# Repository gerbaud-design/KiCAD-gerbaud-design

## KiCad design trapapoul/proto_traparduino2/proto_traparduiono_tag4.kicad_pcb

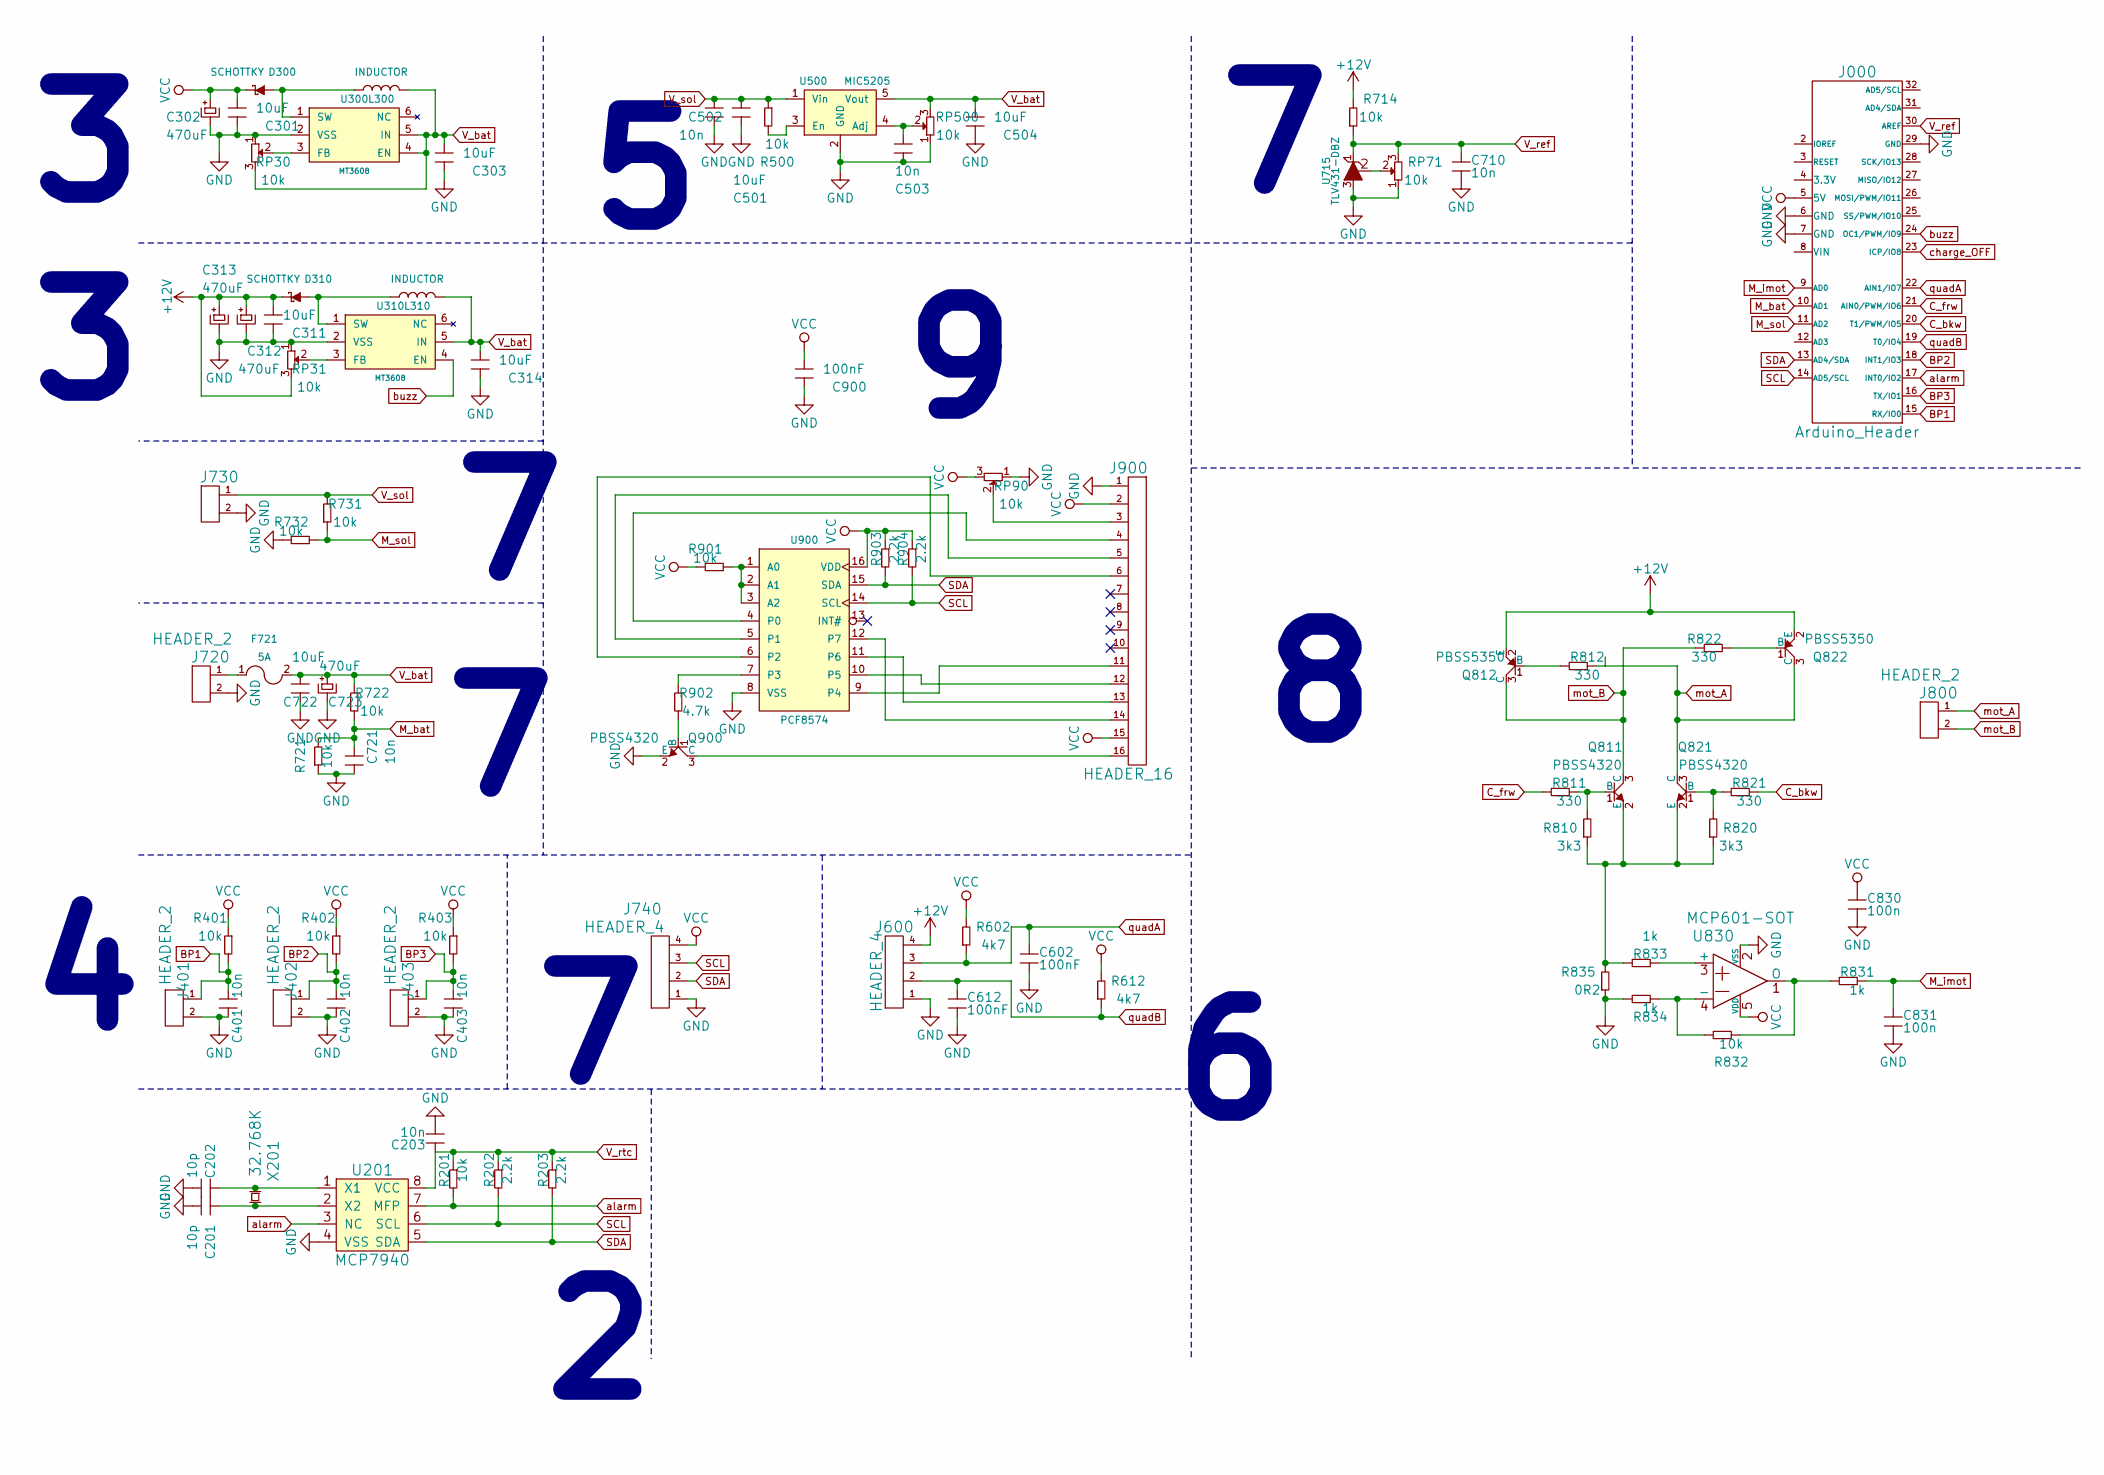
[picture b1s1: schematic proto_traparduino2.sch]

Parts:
C201, C202: 10p; C_1206_HandSoldering
C203, C401, C402, C403, C502, C503, C710, C721: 10n; C_1206_HandSoldering
C301, C303, C311, C314, C501, C504, C722: 10uF; C_1206_HandSoldering
C302, C312, C313, C723: 470uF; C_Radial_D8_L11.5_P3.5
C602, C612, C900: 100nF; C_1206_HandSoldering
C830, C831: 100n; C_1206_HandSoldering
D300, D310: SCHOTTKY; MiniMELF_Handsoldering
F721: 5A; Fuse_SMD1206_HandSoldering
J000: Arduino_Header; arduino_header
J401, J402, J403, J720, J730, J800: HEADER_2; Pin_Header_Straight_1x02
J600, J740: HEADER_4; Pin_Header_Straight_1x04
J900: HEADER_16; Pin_Header_Straight_1x16
L300, L310: INDUCTOR; R_1206_HandSoldering
Q811, Q821, Q900: PBSS4320; SOT-23_Handsoldering
Q812, Q822: PBSS5350; SOT-23_Handsoldering
R201, R401, R402, R403, R500, R714, R721, R722, R731, R732, R832, R901: 10k; R_1206_HandSoldering
R202, R203, R903, R904: 2.2k; R_1206_HandSoldering
R602, R612: 4k7; R_1206_HandSoldering
R810, R820: 3k3; R_1206_HandSoldering
R811, R812, R821, R822: 330; R_1206_HandSoldering
R831, R833, R834: 1k; R_1206_HandSoldering
R835: 0R2; R_1206_HandSoldering
R902: 4.7k; R_1206_HandSoldering
RP30, RP31, RP71, RP90, RP500: 10k; Potentiometer_Triwood_RM-065
U201: MCP7940; SOIC-8-N
U300, U310: MT3608; SOT-23-6_Handsoldering
U500: MIC5205; SOT-23-5_Handsoldering
U715: TLV431-DBZ; SOT-23_Handsoldering
U830: MCP601-SOT; SOT-23-5_Handsoldering
U900: PCF8574; SO-16-W
X201: 32.768K; Crystal_Round_Vertical_3mm_BigPad

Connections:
+12V: C311.1, C312.1, C313.1, D310.2 (K), J600.4, Q812.2 (E), Q822.2 (E), R714.2, RP31.3
BP1: C401.1, J000.15 (RX/IO0), J401.1, R401.2
BP2: C402.1, J000.18 (INT1/IO3), J402.1, R402.2
BP3: C403.1, J000.16 (TX/IO1), J403.1, R403.2
C_bkw: J000.20 (T1/PWM/IO5), R821.1
C_frw: J000.21 (AIN0/PWM/IO6), R811.2
GND: C201.2, C202.2, C203.2, C301.2, C302.2, C303.2, C311.2, C312.2, C313.2, C314.2, C401.2, C402.2, C403.2, C501.2, C502.2, C503.2, C504.2, C602.2, C612.2, C710.2, C721.2, C722.2, C723.2, C830.2, C831.2, C900.2, J000.6 (GND), J000.7 (GND), J000.29 (GND), J401.2, J402.2, J403.2, J600.1, J720.2, J730.2, J740.1, J900.1, Q900.2 (E), R721.1, R732.2, R834.2, R835.1, RP30.1, RP31.1, RP71.1, RP90.1, RP500.1, U201.4 (VSS), U300.2 (VSS), U310.2 (VSS), U500.2 (GND), U715.3 (A), U830.2 (VSS), U900.8 (VSS)
M_bat: C721.1, J000.10 (AD1), R721.2, R722.2
M_imot: C831.1, J000.9 (AD0), R831.1
M_sol: J000.11 (AD2), R731.1, R732.1
unnamed: C201.1, U201.2 (X2), X201.2
unnamed: C202.1, U201.1 (X1), X201.1
unnamed: C503.1, RP500.2, U500.4 (Adj)
unnamed: D300.1 (A), L300.1, U300.1 (SW)
unnamed: D310.1 (A), L310.1, U310.1 (SW)
unnamed: F721.1, J720.1
unnamed: J900.3, RP90.2
unnamed: J900.4, U900.4 (P0)
unnamed: J900.5, U900.5 (P1)
unnamed: J900.6, U900.6 (P2)
unnamed: J900.11, U900.9 (P4)
unnamed: J900.12, U900.10 (P5)
unnamed: J900.13, U900.11 (P6)
unnamed: J900.14, U900.12 (P7)
unnamed: J900.16, Q900.3 (C)
unnamed: Q811.1 (B), R810.2, R811.1
unnamed: Q811.2 (E), Q821.2 (E), R810.1, R820.1, R833.2, R835.2
unnamed: Q812.1 (B), R812.2
unnamed: Q821.1 (B), R820.2, R821.2
unnamed: Q822.1 (B), R822.2
unnamed: Q900.1 (B), R902.2
unnamed: R500.2, U500.3 (En)
unnamed: R831.2, R832.1, U830.1 (O)
unnamed: R832.2, R834.1, U830.4 (-)
unnamed: R833.1, U830.3 (+)
unnamed: R901.1, U900.1 (A0), U900.2 (A1), U900.3 (A2)
unnamed: R902.1, U900.7 (P3)
unnamed: RP30.2, U300.3 (FB)
unnamed: RP31.2, U310.3 (FB)
unnamed: RP71.2, U715.2 (Ref)
SCL: J000.14 (AD5/SCL), J740.3, R202.2, R904.2, U201.6 (SCL), U900.14 (SCL)
SDA: J000.13 (AD4/SDA), J740.2, R203.2, R903.2, U201.5 (SDA), U900.15 (SDA)
VCC: C301.1, C302.1, C830.1, C900.1, D300.2 (K), J000.5 (5V), J740.4, J900.2, J900.15, R401.1, R402.1, R403.1, R602.2, R612.2, R901.2, R903.1, R904.1, RP90.3, U830.5 (VDD), U900.16 (VDD)
V_bat: C303.1, C314.1, C504.1, C722.1, C723.1, F721.2, L300.2, L310.2, R722.1, RP30.3, RP500.3, U300.4 (EN), U300.5 (IN), U310.5 (IN), U500.5 (Vout)
V_ref: C710.1, J000.30 (AREF), R714.1, RP71.3, U715.1 (K)
V_rtc: C203.1, R201.1, R202.1, R203.1, U201.8 (VCC)
V_sol: C501.1, C502.1, J730.1, R500.1, R731.2, U500.1 (Vin)
alarm: J000.17 (INT0/IO2), R201.2, U201.3 (NC), U201.7 (MFP)
buzz: J000.24 (OC1/PWM/IO9), U310.4 (EN)
mot_A: J800.1, Q821.3 (C), Q822.3 (C), R812.1
mot_B: J800.2, Q811.3 (C), Q812.3 (C), R822.1
quadA: C602.1, J000.22 (AIN1/IO7), J600.3, R602.1
quadB: C612.1, J000.19 (T0/IO4), J600.2, R612.1

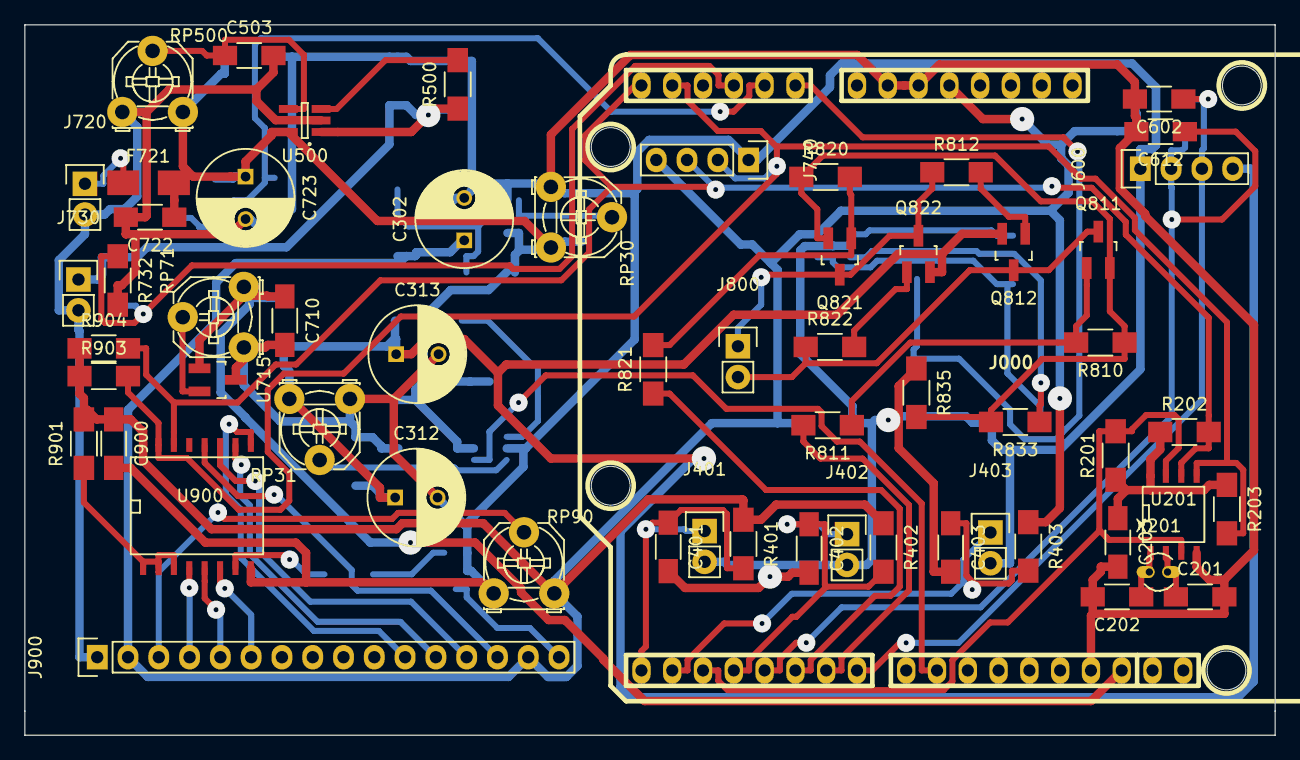
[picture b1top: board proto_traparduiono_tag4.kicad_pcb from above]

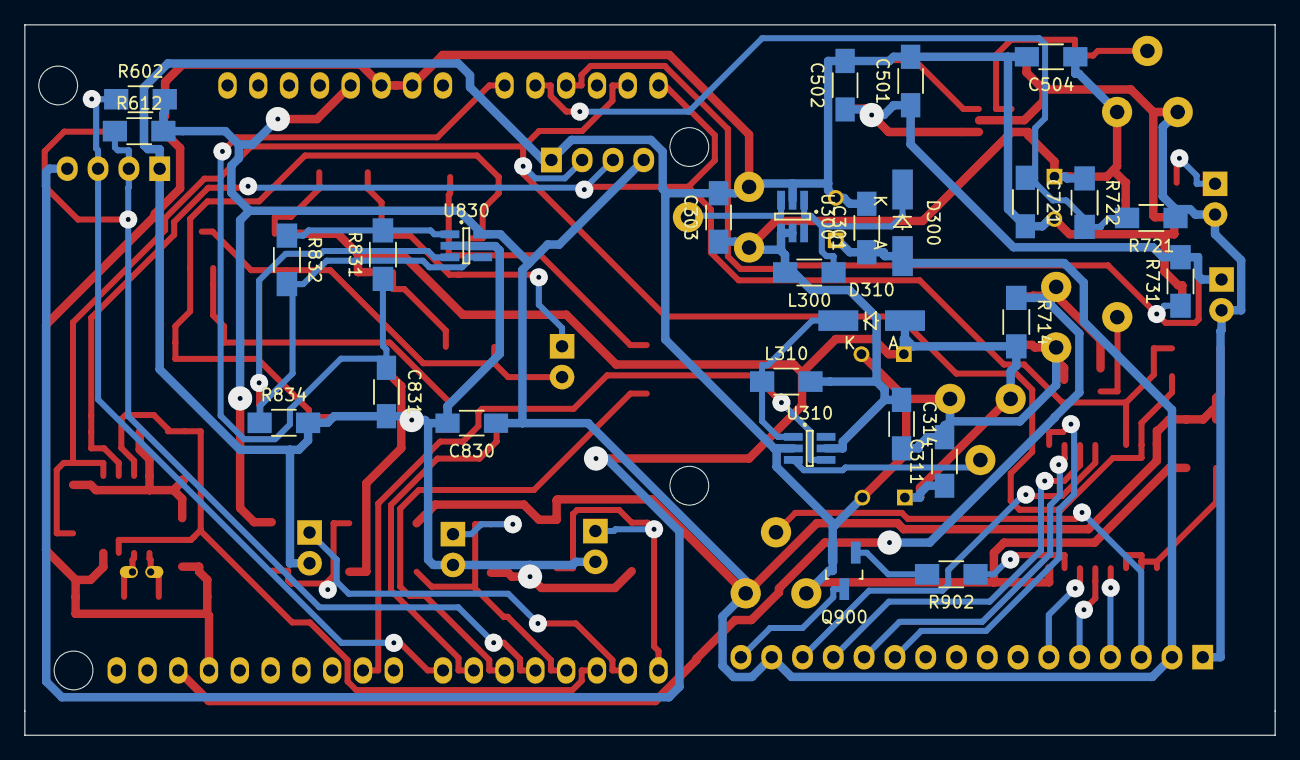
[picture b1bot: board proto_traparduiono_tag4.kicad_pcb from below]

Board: 2 copper layers, 103.1 x 58.6 mm, 88 parts (28 on the bottom side), 53 nets.

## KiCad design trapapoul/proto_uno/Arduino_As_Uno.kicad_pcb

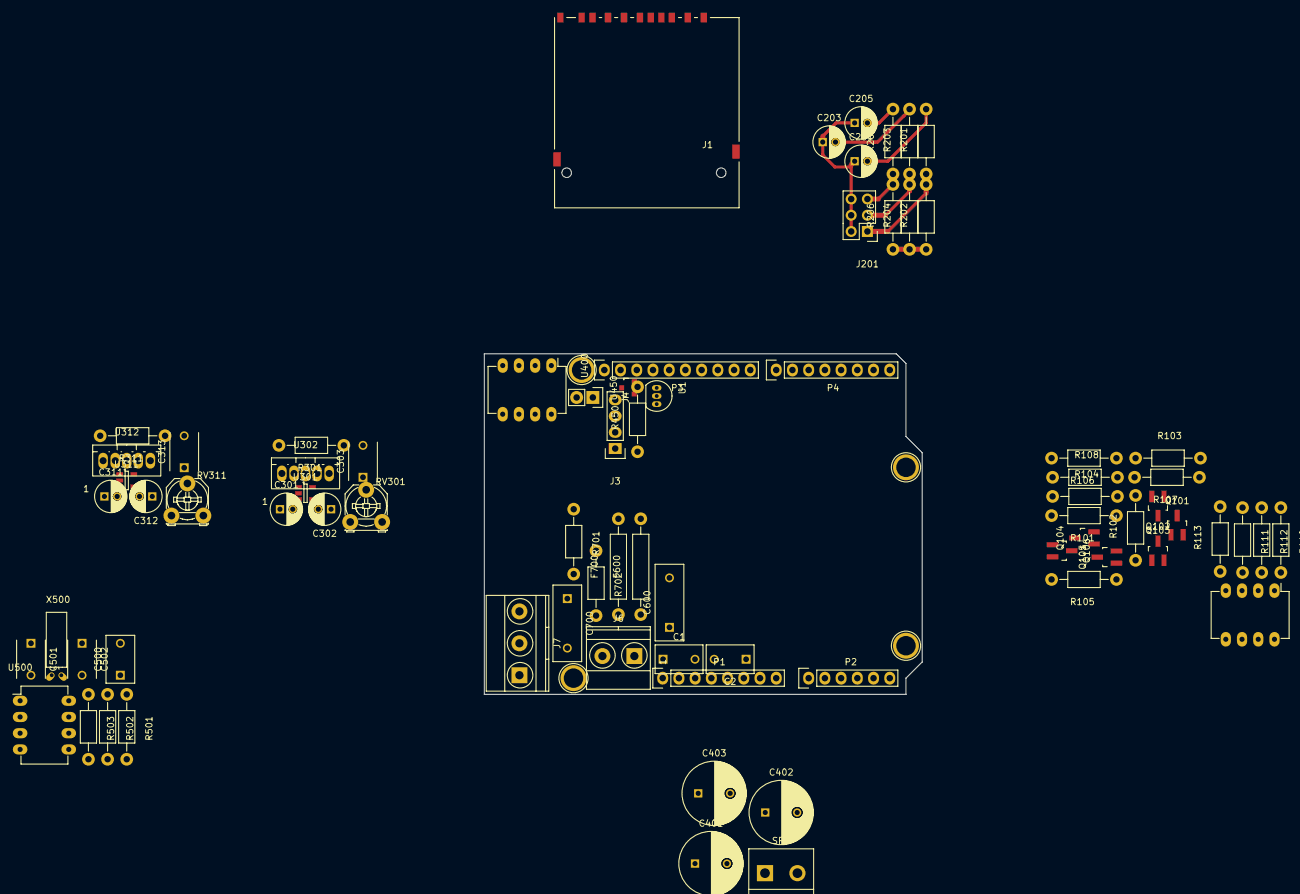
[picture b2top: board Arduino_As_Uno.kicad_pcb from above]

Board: 2 copper layers, 68.6 x 53.3 mm, 80 parts (0 on the bottom side), 46 nets.

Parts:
C1, C2, C500: 100n; C_Disc_D7.5_P5
C201, C203, C205, C301, C302, C311, C312: 1u; C_Radial_D5_L11_P2
C303: 470pF; C_Disc_D6_P5
C313: 470p; C_Disc_D6_P5
C401, C402, C403: 100u; C_Radial_D10_L13_P5
C501, C502: 10p; C_Disc_D6_P5
C600: 100nF; C_Disc_D12_P7.75
C700: 100n; C_Disc_D12_P7.75
F600: 1A; Resistor_Horizontal_RM15mm
F700: 3A; Resistor_Horizontal_RM15mm
J1: MICROSD; SD_Card_Receptacle
J3: CONN_4; Pin_Header_Straight_1x04
J4: CONN_2; Pin_Header_Straight_1x02
J6: CONN_2; TerminalBlock_Pheonix_MKDS1.5-2pol
J7: CONN_3; TerminalBlock_Pheonix_MKDS1.5-3pol
J201: CONN_3X2; Pin_Header_Straight_2x03
P1: Power; Socket_Strip_Arduino_1x08
P2: Analog; Socket_Strip_Arduino_1x06
P3: Digital; Socket_Strip_Arduino_1x10
P4: Digital; Socket_Strip_Arduino_1x08
P5, P6, P7, P8: CONN_01X01; Arduino_1pin
Q101, Q102, Q104, Q105: PBSS5350; SOT-23_Handsoldering
Q103, Q106: PBSS4320; SOT-23_Handsoldering
R101, R103, R104, R106: 100; Resistor_Horizontal_RM10mm
R102, R105, R111, R112, R301: 1k; Resistor_Horizontal_RM10mm
R107, R108, R110, R201, R202, R203, R204, R205, R206, R311, R501, R701: 10k; Resistor_Horizontal_RM10mm
R113: 0.2; Resistor_Horizontal_RM10mm
R450: 100k; Resistor_Horizontal_RM10mm
R502, R503: 2.2k; Resistor_Horizontal_RM10mm
R702: 4k7; Resistor_Horizontal_RM10mm
RV301, RV311: 200k; Potentiometer_Triwood_RM-065
SP4: SPEAKER; bornier2
U1: TL431TH; TO-92_Inline_Narrow_Oval
U110: aop; DIP-8_W7.62mm_LongPads
U301, U311: MIC5205; SOT-23-5
U302, U312: MIC1825; Pentawatt_Neutral_Straight_Vertical_TO220-5-T05A
U400: CAT24C64; DIP-8_W7.62mm_LongPads
U450: TL431LP; SOT-23
U500: MCP7940; DIP-8_W7.62mm_LongPads
X500: 32.768KHz; Crystal_Round_Horizontal_3mm_BigPad

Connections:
+3.3V: C1.2, C312.1, C500.1, J1.4, J3.1, J4.1, P1.4, R202.1, R204.1, R206.1, R450.1, R501.1, R502.1, R503.1, RV311.3, U110.8, U311.5, U312.4, U400.8, U500.8
+5V: C2.2, P1.5
A_REF: P3.3, R450.2, U1.1, U1.3, U450.1, U450.2
Alarm_clock: P4.6, R501.2, U500.7
BUTTON_LOW: C205.2, P4.3, R205.2
BUTTON_MID: C203.2, P4.4, R203.2
BUTTON_UP: C201.2, P4.5, R201.2
Buzz: C401.1, C402.1, C403.1, P4.2
Charge_ON: P3.9, R301.1
GND: C1.1, C2.1, C201.1, C203.1, C205.1, C301.2, C302.2, C303.2, C311.2, C312.2, C313.2, C500.2, C501.1, C502.1, C600.1, C700.1, J1.6, J3.4, J6.2, J7.2, J201.2, J201.4, J201.6, P1.6, P1.7, P3.4, R112.1, R113.1, R702.2, RV301.1, RV311.1, SP4.2, U1.2, U110.4, U301.2, U302.3, U311.2, U312.3, U400.1, U400.2, U400.3, U400.4, U450.3, U500.4
I2C_SCL: J3.3, P2.6, P3.1, R502.2, U400.6, U500.6
I2C_SDA: J3.2, P2.5, P3.2, R503.2, U400.5, U500.5
ICSP2_MISO: J1.7, P3.6
ICSP2_MOSI: J1.3, P3.7
ICSP2_SCK: J1.5, P3.5
MOT_A: Q104.3, Q106.3, R101.2, R105.2
MOT_B: Q101.3, Q103.3, R102.2, R104.2
MOT_BKW: P4.7, R106.2
MOT_FRW: P4.8, R103.1
Mes_bat: P2.2, R701.2, R702.1
Mes_mot: P2.3, R110.2, U110.1
unnamed: C303.1, RV301.2, U301.4, U302.5
unnamed: C313.1, RV311.2, U311.4, U312.5
unnamed: C401.2, C402.2, C403.2, SP4.1
unnamed: C501.2, U500.1, X500.1
unnamed: C502.2, U500.2, X500.2
unnamed: C600.2, F600.1, J6.1
unnamed: C700.2, F700.1, J7.1
unnamed: J4.2, U400.7
unnamed: J201.1, R201.1, R202.2
unnamed: J201.3, R203.1, R204.2
unnamed: J201.5, R205.1, R206.2
unnamed: Q101.1, Q102.3, R101.1
unnamed: Q102.1, R102.1
unnamed: Q103.1, R103.2, R107.1
unnamed: Q103.2, Q106.2, R107.2, R108.1, R111.1, R113.2
unnamed: Q104.1, Q105.3, R104.1
unnamed: Q105.1, R105.1
unnamed: Q106.1, R106.1, R108.2
unnamed: R110.1, R112.2, U110.2
unnamed: R111.2, U110.3
unnamed: R301.2, U301.3, U302.1
unnamed: R311.2, U311.3, U312.1
SDCARD_CS: J1.2, P3.8
V_bat: C302.1, F700.2, Q101.2, Q102.2, Q104.2, Q105.2, R311.1, R701.1, RV301.3, U301.5, U302.4, U311.1, U312.2
V_sol: C301.1, F600.2, U301.1, U302.2
